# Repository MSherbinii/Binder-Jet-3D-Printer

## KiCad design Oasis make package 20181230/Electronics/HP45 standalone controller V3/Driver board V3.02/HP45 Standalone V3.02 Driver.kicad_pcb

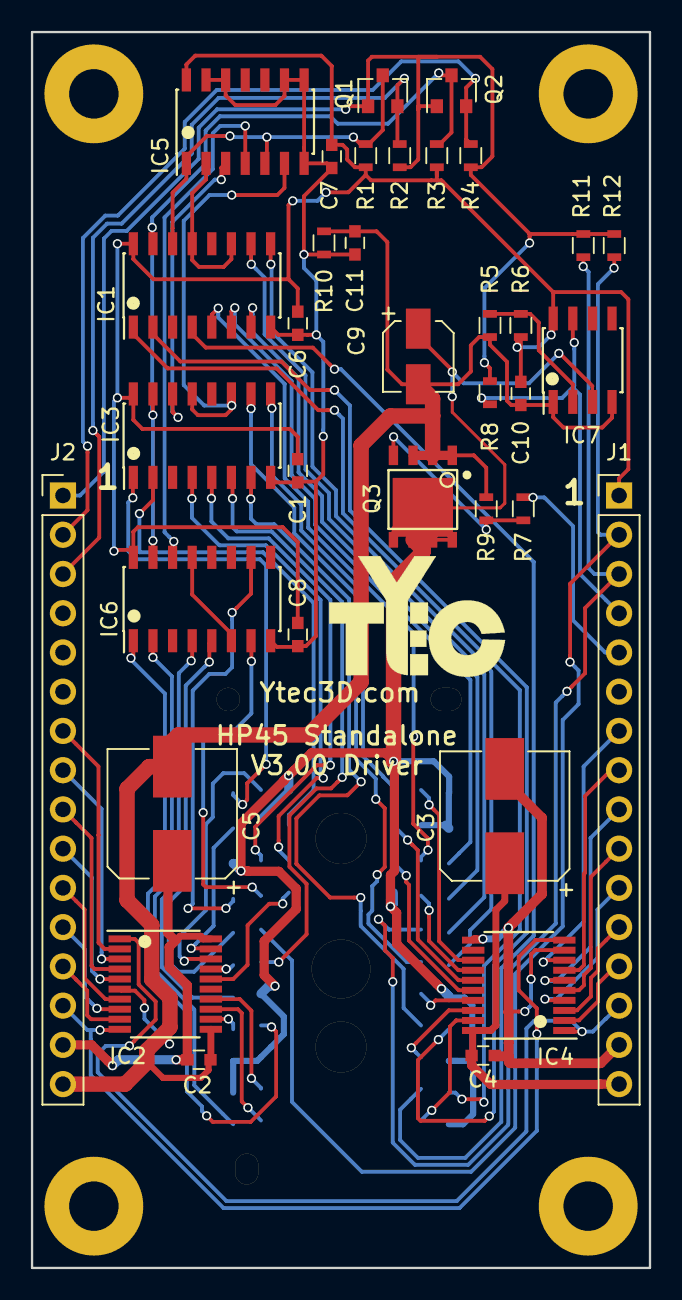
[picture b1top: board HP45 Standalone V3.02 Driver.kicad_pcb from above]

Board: 2 copper layers, 40.0 x 80.0 mm, 36 parts (1 on the bottom side), 73 nets.

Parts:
C1, C6, C7, C8, C10, C11: 0.1uF; C_0603
C2, C4: 1uF; C_0603
C3, C5: 100uF; CP_Elec_8x10
C9: 1uF; CP_Elec_4x5.8
Con1: HP45_connector; HP45_SMD_connector
IC1, IC3, IC6: HEF4017; SOIC-16_3.9x9.9mm_Pitch1.27mm
IC2, IC4: TLC59213; TSSOP-20_4.4x6.5mm_Pitch0.65mm
IC5: HCF4081; SOIC-14_3.9x8.7mm_Pitch1.27mm
IC7: LM311; SOIC-8_3.9x4.9mm_Pitch1.27mm
J1, J2: CONN_01X16; Socket_Strip_Straight_1x16_Pitch2.54mm
Q1, Q2: Q_NMOS_GSD; SOT-23
Q3: Q_NMOS_SGD; SO-8_PowerPAK
R1, R2, R3, R4, R9, R10: 2.2k; R_0603
R5: 1.2k; R_0603
R6, R8: 10k; R_0603
R7, R11, R12: 330; R_0603

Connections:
+3V3: J2.1, Q1.1, Q2.1, R2.2, R4.2, R8.1, R11.2, R12.2
+12V: C1.1, C6.1, C7.1, C8.1, C10.1, IC1.16, IC3.16, IC5.14, IC6.16, IC7.8, J1.1, R1.2, R3.2, R6.1
/ARST: IC1.15, IC3.15, IC6.15, Q2.3, R3.1
/C10X: Con1.28, J1.3, R11.1
/CACLK: J2.3, Q1.2, R2.1
/CARST: J2.2, Q2.2, R4.1
/CP00: IC2.4, J2.9
/CP01: IC4.4, J1.11
/CP02: IC2.9, J2.13
/CP03: IC4.3, J1.12
/CP04: IC2.7, J2.11
/CP05: IC4.2, J1.13
/CP06: IC2.8, J2.12
/CP07: IC4.8, J1.7
/CP08: IC2.3, J2.8
/CP09: IC4.6, J1.9
/CP10: IC2.2, J2.7
/CP11: IC4.5, J1.10
/CP12: IC2.5, J2.10
/CP13: IC4.7, J1.8
/CTSR: Con1.27, J1.2, R12.1
/HA00: Con1.25, IC6.5
/HA01: Con1.29, IC6.10
/HA02: Con1.23, IC3.6
/HA03: Con1.31, IC6.7
/HA04: Con1.17, IC6.4
/HA05: Con1.37, IC3.5
/HA06: Con1.15, IC6.1
/HA07: Con1.39, IC3.4
/HA08: Con1.1, IC6.2
/HA09: Con1.45, IC3.2
/HA10: Con1.6, IC1.1
/HA11: Con1.47, IC3.1
/HA12: Con1.8, IC1.4
/HA13: Con1.52, IC3.9
/HA14: Con1.14, IC1.2
/HA15: Con1.38, IC1.5
/HA16: Con1.16, IC3.7
/HA17: Con1.36, IC1.6
/HA18: Con1.22, IC1.9
/HA19: Con1.30, IC1.7
/HA20: Con1.24, IC3.10
/HA21: Con1.26, IC1.10
/HENA: J1.5, R7.2
/HGND: C9.1, Con1.2, Con1.5, Con1.9, Con1.10, Con1.11, Con1.18, Con1.19, Con1.34, Con1.35, Con1.42, Con1.43, Con1.44, Con1.48, Con1.51, IC7.3, Q3.3
/HP00: Con1.21, IC2.17
/HP01: Con1.20, IC4.17
/HP02: Con1.13, IC2.12
/HP03: Con1.12, IC4.18
/HP04: Con1.7, IC2.14
/HP05: Con1.4, IC4.19
/HP06: Con1.3, IC2.13
/HP07: Con1.50, IC4.13
/HP08: Con1.49, IC2.18
/HP09: Con1.46, IC4.15
/HP10: Con1.41, IC2.19
/HP11: Con1.40, IC4.16
/HP12: Con1.33, IC2.16
/HP13: Con1.32, IC4.14
/NCHECK: IC7.7, J1.4, R8.2
/PCLK: IC2.10, IC4.10, J2.14
/PCLR: IC2.1, IC4.1, J1.14
AGND: C1.2, C6.2, C7.2, C8.2, C11.1, IC1.8, IC3.8, IC5.7, IC5.8, IC5.9, IC5.12, IC5.13, IC6.8, R10.1
GND: C2.2, C3.2, C4.2, C5.2, C9.2, C10.2, C11.2, IC2.6, IC2.11, IC4.9, IC4.11, IC7.1, IC7.4, J1.15, J2.16, Q3.1, R5.2, R9.1, R10.2
unnamed: IC1.11, IC1.13, IC5.2
unnamed: IC1.14, IC5.1, IC5.5, Q1.3, R1.1
unnamed: IC3.11, IC3.13, IC5.6
unnamed: IC3.14, IC5.3
unnamed: IC5.4, IC6.14
unnamed: IC6.6, IC6.13
unnamed: IC7.2, R5.1, R6.2
unnamed: Q3.2, R7.1, R9.2
VHead: C2.1, C3.1, C4.1, C5.1, IC2.20, IC4.20, J1.16, J2.15

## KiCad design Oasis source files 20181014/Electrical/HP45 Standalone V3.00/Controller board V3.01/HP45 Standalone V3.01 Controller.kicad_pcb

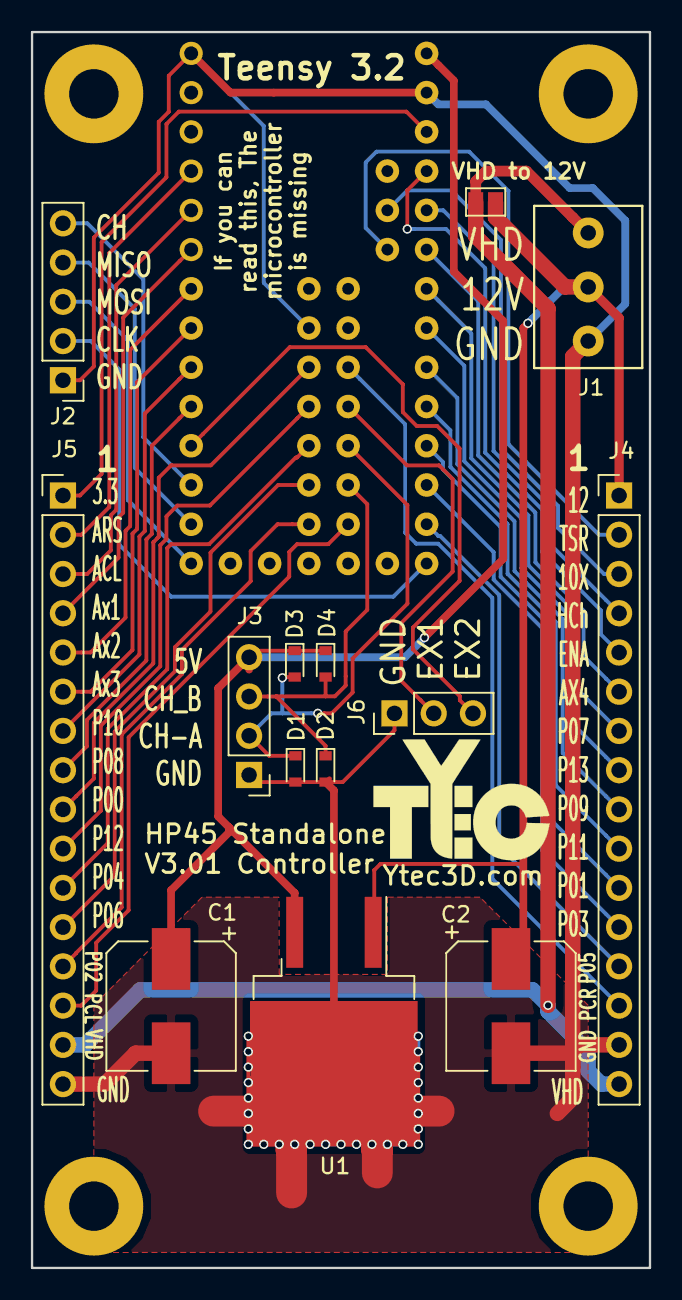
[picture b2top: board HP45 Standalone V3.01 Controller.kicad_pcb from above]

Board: 2 copper layers, 40.0 x 80.0 mm, 15 parts (0 on the bottom side), 39 nets.

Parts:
C1, C2: 100uF; CP_Elec_8x10
D1, D2, D3, D4: D; D_0603
J1: Screw_Terminal_1x03; 3.5mm_screw_terminal
J2: CONN_01X05; Socket_Strip_Straight_1x05_Pitch2.54mm
J3: CONN_01X04; Socket_Strip_Straight_1x04_Pitch2.54mm
J4, J5: CONN_01X16; Socket_Strip_Straight_1x16_Pitch2.54mm
J6: CONN_01X03; Socket_Strip_Straight_1x03_Pitch2.54mm
JP1: Jumper; GS2
U1: 7805; TO-263-2
uC1: Teensy_3.2_custom

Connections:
+3V3: J5.1, uC1.48
+5V: C1.1, D3.1, D4.1, J3.4, U1.3, uC1.50
+12V: C2.1, J1.2, J4.1, JP1.2, U1.1
/10X: J4.3, uC1.44
/ACLK: J5.3, uC1.5
/ARST: J5.2, uC1.4
/Aux1: J5.4, uC1.6
/Aux2: J5.5, uC1.7
/Aux3: J5.6, uC1.9
/Aux4: J4.6, uC1.43
/CH_A: D1.1, D3.2, J3.2, uC1.32
/CH_B: D2.1, D4.2, J3.3, uC1.30
/CS: J2.5, uC1.17
/Ext1: J6.2, uC1.34
/Ext2: J6.3, uC1.15
/HENA: J4.5, uC1.47
/MISO: J2.4, uC1.19
/MOSI: J2.3, uC1.21
/NCHECK: J4.4, uC1.45
/P00: J5.9, uC1.12
/P01: J4.11, uC1.33
/P02: J5.13, uC1.20
/P03: J4.12, uC1.31
/P04: J5.11, uC1.16
/P05: J4.13, uC1.29
/P06: J5.12, uC1.18
/P07: J4.7, uC1.41
/P08: J5.8, uC1.13
/P09: J4.9, uC1.37
/P10: J5.7, uC1.11
/P11: J4.10, uC1.35
/P12: J5.10, uC1.14
/P13: J4.8, uC1.39
/PCLK: J5.14, uC1.28
/PCLR: J4.14, uC1.36
/SCLK: J2.2, uC1.27
/TSR: J4.2, uC1.42
GND: C1.2, C2.2, D1.2, D2.2, J1.1, J2.1, J3.1, J4.15, J5.16, J6.1, U1.2, uC1.1, uC1.10, uC1.49
VHEAD: J1.3, J4.16, J5.15, JP1.1

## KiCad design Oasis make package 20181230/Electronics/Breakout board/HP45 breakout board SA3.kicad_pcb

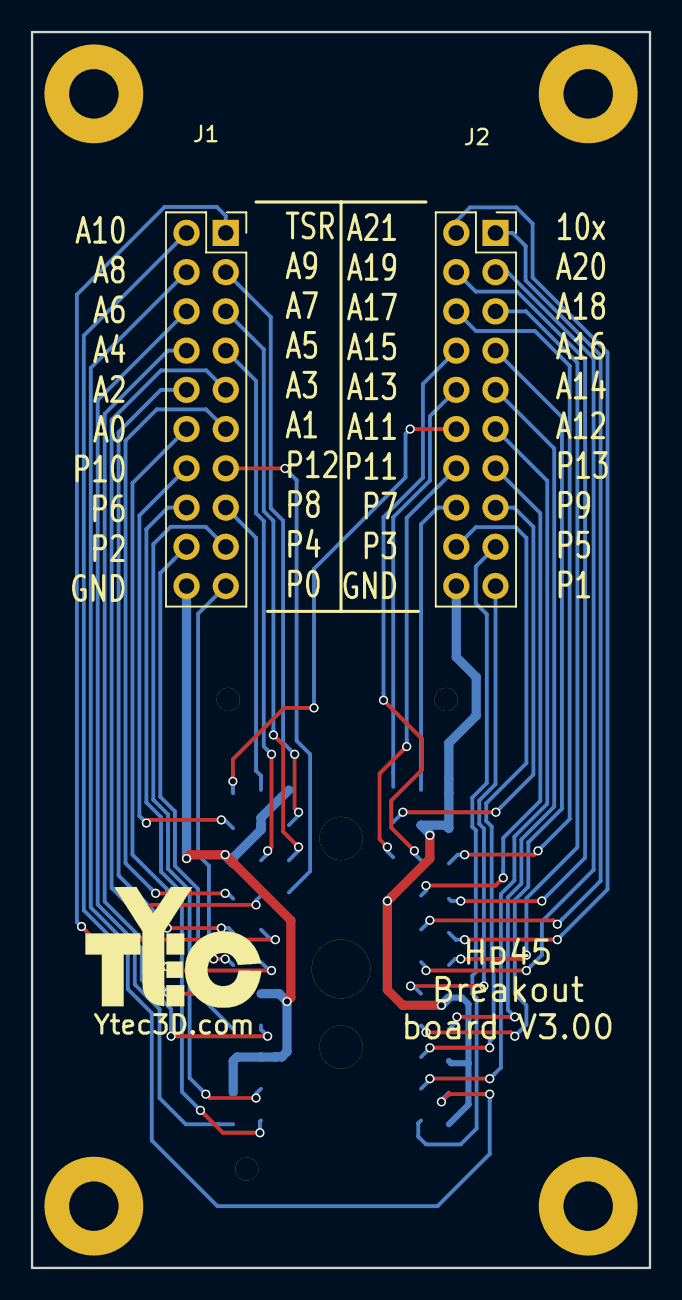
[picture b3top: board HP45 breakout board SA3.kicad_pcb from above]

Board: 2 copper layers, 40.0 x 80.0 mm, 3 parts (1 on the bottom side), 39 nets.

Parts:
Con1: HP45_connector; HP45_SMD_connector
J1, J2: CONN_02X10; Socket_Strip_Straight_2x10_Pitch2.54mm

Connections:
/10X: Con1.28, J2.1
/A0: Con1.25, J1.12
/A1: Con1.29, J1.11
/A2: Con1.23, J1.10
/A3: Con1.31, J1.9
/A4: Con1.17, J1.8
/A5: Con1.37, J1.7
/A6: Con1.15, J1.6
/A7: Con1.39, J1.5
/A8: Con1.1, J1.4
/A9: Con1.45, J1.3
/A10: Con1.6, J1.2
/A11: Con1.47, J2.12
/A12: Con1.8, J2.11
/A13: Con1.52, J2.10
/A14: Con1.14, J2.9
/A15: Con1.38, J2.8
/A16: Con1.16, J2.7
/A17: Con1.36, J2.6
/A18: Con1.22, J2.5
/A19: Con1.30, J2.4
/A20: Con1.24, J2.3
/A21: Con1.26, J2.2
/HGND: Con1.2, Con1.5, Con1.9, Con1.10, Con1.11, Con1.18, Con1.19, Con1.34, Con1.35, Con1.42, Con1.43, Con1.44, Con1.48, Con1.51, J1.20, J2.20
/P0: Con1.21, J1.19
/P1: Con1.20, J2.19
/P2: Con1.13, J1.18
/P3: Con1.12, J2.18
/P4: Con1.7, J1.17
/P5: Con1.4, J2.17
/P6: Con1.3, J1.16
/P7: Con1.50, J2.16
/P8: Con1.49, J1.15
/P9: Con1.46, J2.15
/P10: Con1.41, J1.14
/P11: Con1.40, J2.14
/P12: Con1.33, J1.13
/P13: Con1.32, J2.13
/TSR: Con1.27, J1.1

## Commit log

2022-12-10 Create Oasis source files 20210523
2022-12-10 Create 1
